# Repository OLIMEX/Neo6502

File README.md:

# Neo6502
Neo6502 Modern Retro Computer with W65C02S processor and RP2040 memory and peripherals emulator

Neo6502 is small board with dimensions 80x55mm.

it consist of real W65C02S processor and RP2040 which emulates RAM memory, video, keyboard, SPI, I2C, UART, GPIOs, Sound

## Intro

W65C02S lives in The Matrix and thinks there is real RAM and other interfaces around it, but the truth is that all this is emulation of the real life. The RP2040 emulates the RAM memory, video, IO and even clock the W65C02S by PWM.

## Features

Neo6502 has these features:

* W65C02S processor
* RP2040 SOC with 2MB Flash
* DVI video on HDMI connector
* USB host for keyboard
* Audio 3.5mm output
* Speaker with enable jumper
* USB-C for power supply
* UEXT connector with I2C, UART and SPI
* 40 pin 6502 bus connector with all W65C02 signals
* Dimensions 80x55mm
* 4 mount holes

## Licenses

* Hardware is released under CERN Open Hardware Licence Version 2 - Strongly Reciprocal, all silkscreen credits to Olimex should remain;
* Software is released under GPL3 Licensee
* Documentation is released under CC BY-SA 3.0

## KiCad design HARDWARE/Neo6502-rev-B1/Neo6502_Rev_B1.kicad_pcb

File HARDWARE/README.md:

Contains hardware design files for Olimex Neo6502

Board was designed with free Open Source CAD software - KiCAD, if you have trouble opening the design files use newest KiCAD version.

Folder "3D printed Case" contains STL files for multi material 3D printing of the encolosure.

STL files are designed with Fusion 360

Notable hardware revision changes:

revision B1
======
1. Added diode 1N5819/S4 on FUSE1 pads to enable 5V on HDMI (diode is used to prevent HDMI powering the board). You can try this adjustmest if you have older revision (with nothing placed over FUSE1) and problems with monitor, remember diode has direction and cathode has to be towards the HDMI connector.

revision B
======

1. Changed values P-B-V-40-LF and P-B-V-10-LF;
2. R7 set to 47R/R1206;
3. Added SWITCH1 for the speaker and signals go to the UEXT in case somebody needs them;
4. Added Neo6502 logo;
5. R1 changed NA to 10K;
6. Added attributions names and e-mail at the bottom;
7. C15 and C16 now 18pF;
8. A lot of small adjustmets to reduce soldering problems and yield.

revision A
======

Initial release.

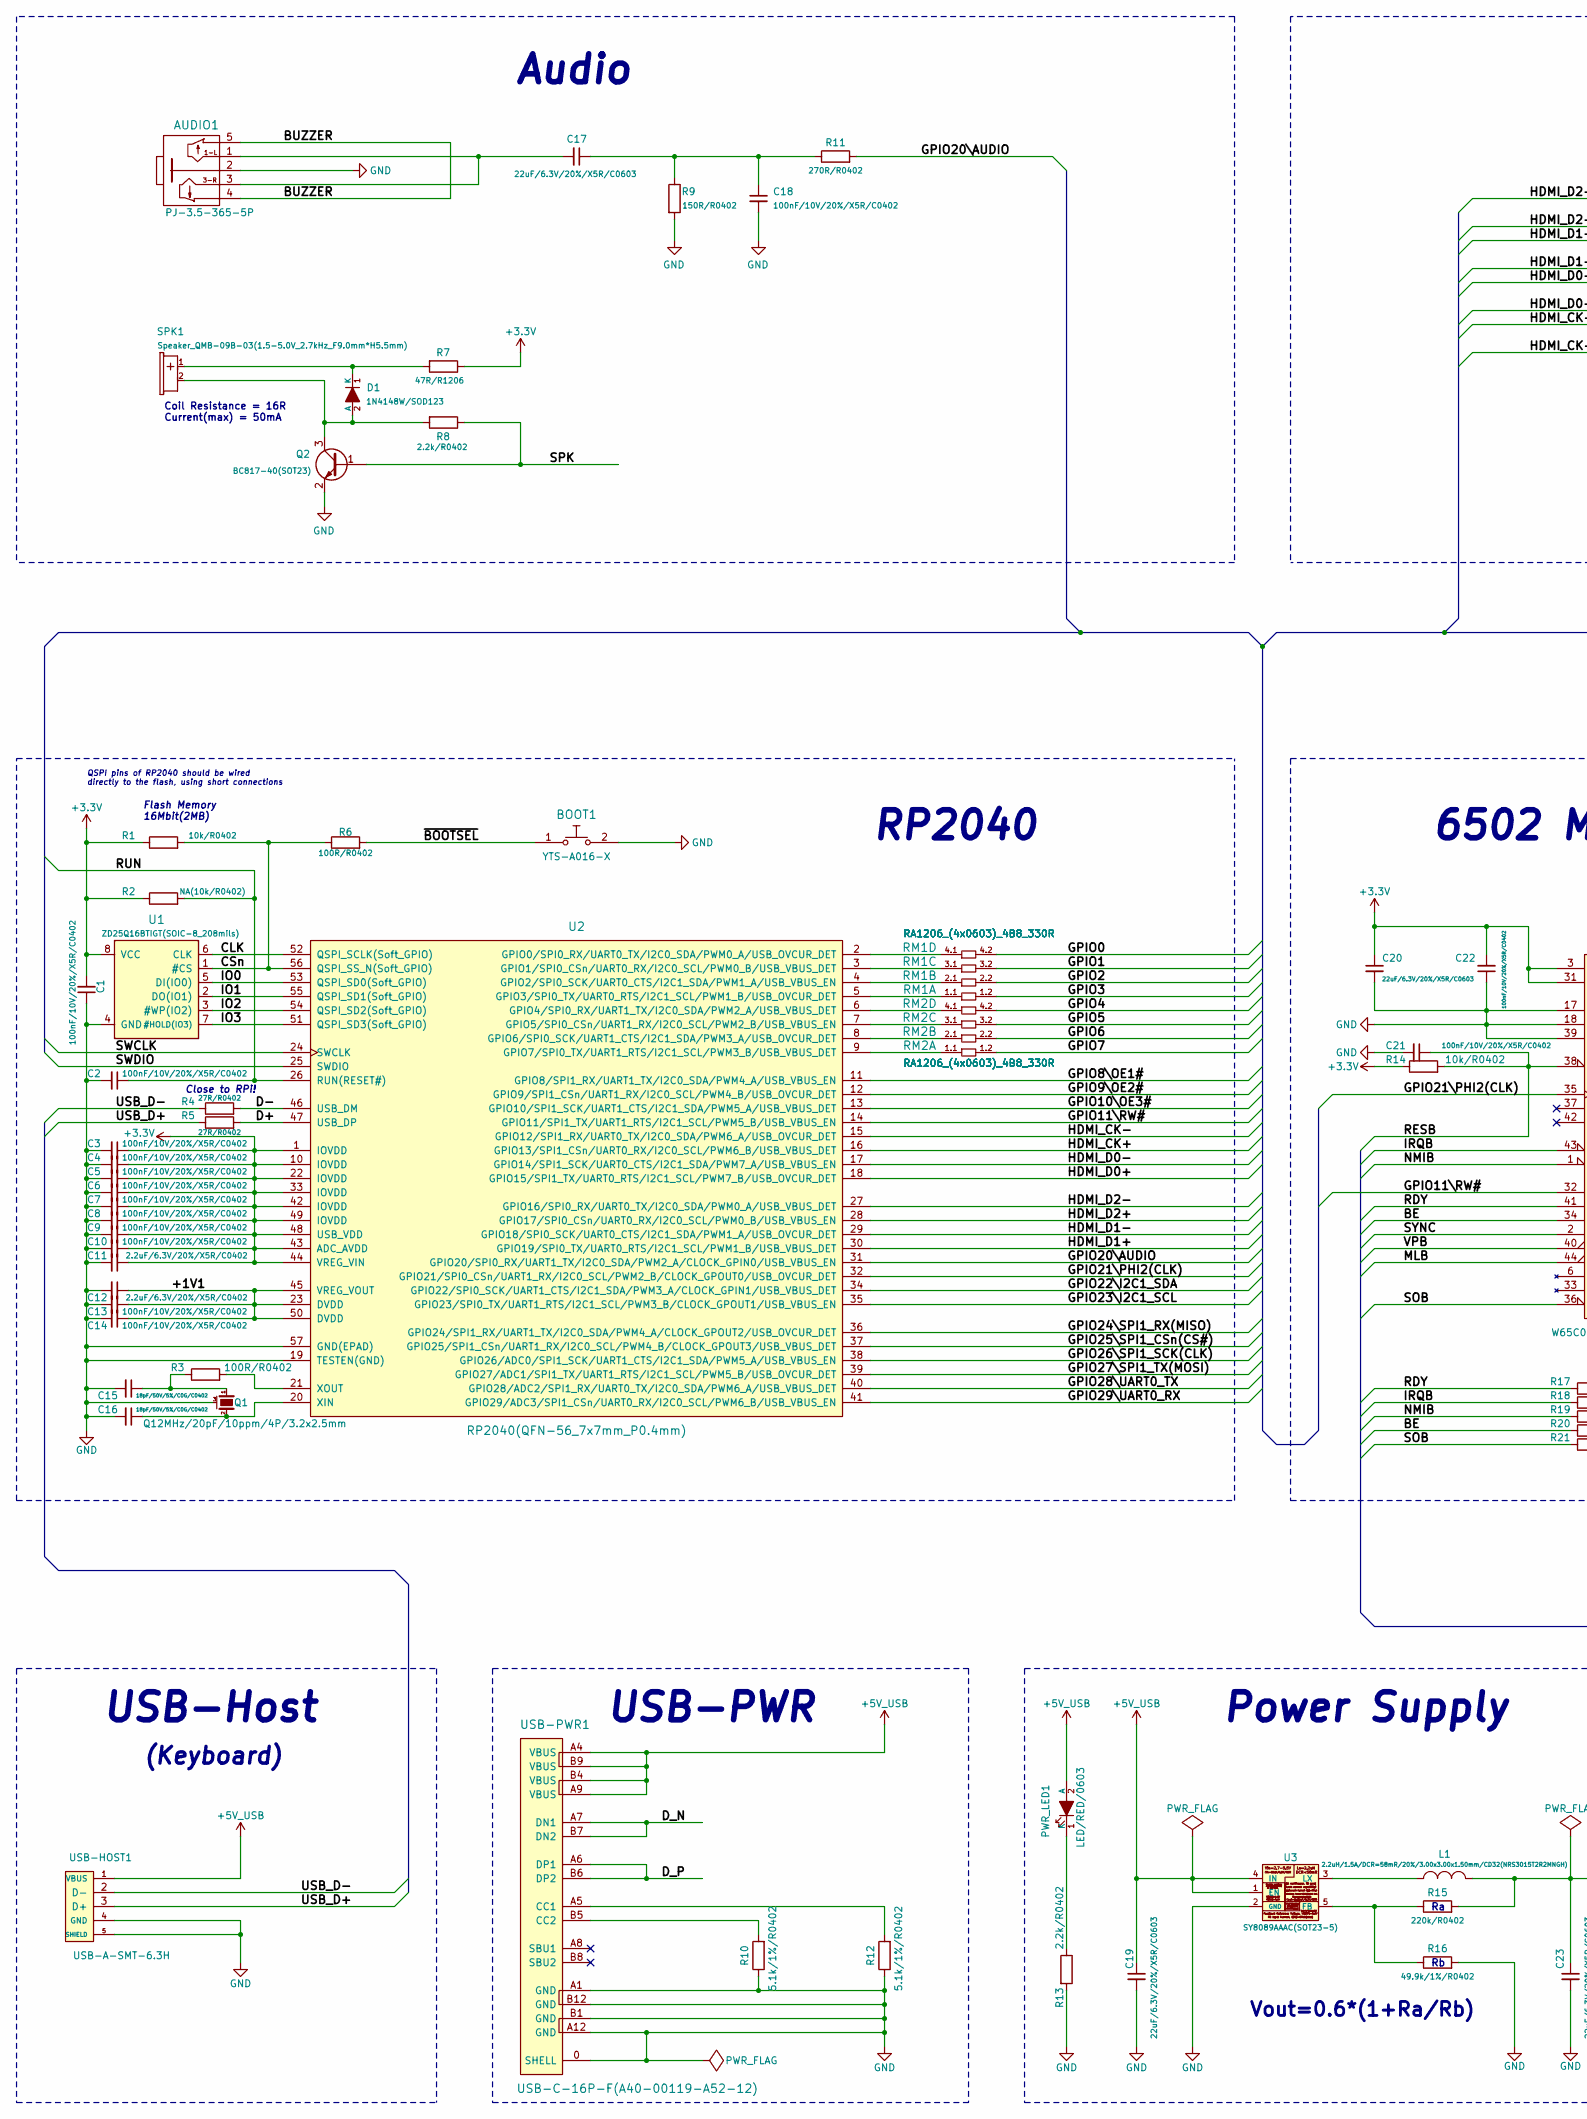
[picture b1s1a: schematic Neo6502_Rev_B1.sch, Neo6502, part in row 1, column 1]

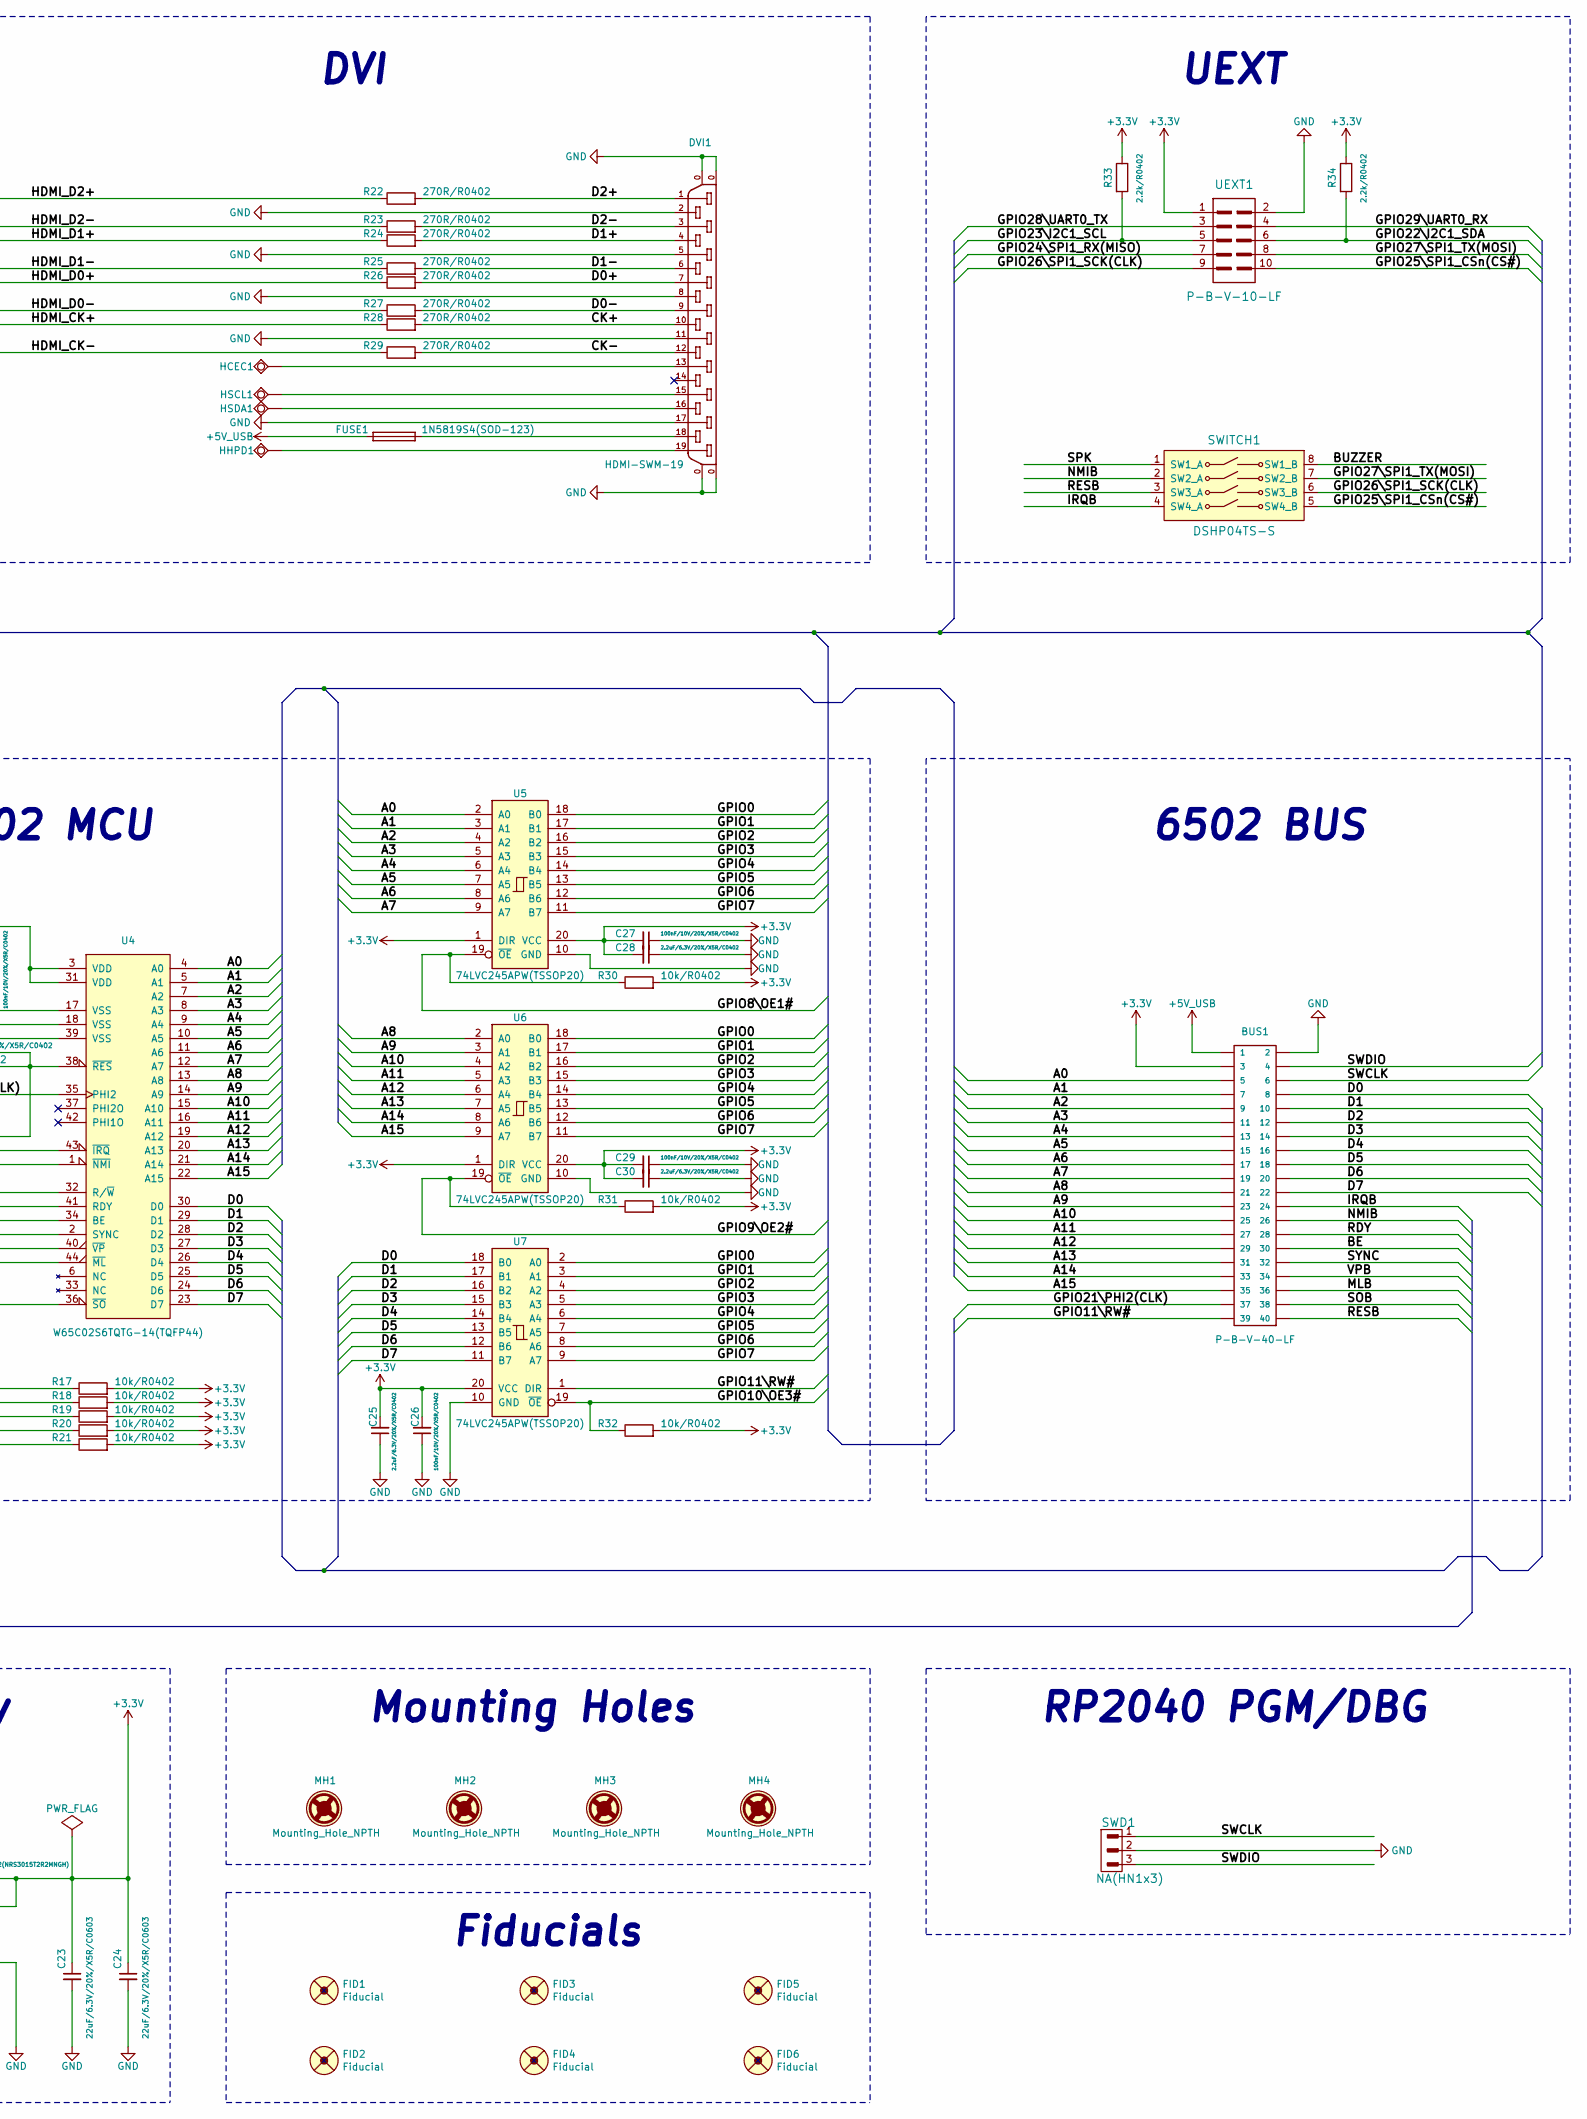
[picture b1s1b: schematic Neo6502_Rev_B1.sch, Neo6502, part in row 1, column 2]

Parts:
AUDIO1: PJ-3.5-365-5P; SCJ325P00XG0B02G
BOOT1: YTS-A016-X
BUS1: P-B-V-40-LF; GBH-254-SMT-40
C1, C2, C3, C4, C5, C6, C7, C8, C9, C10, C13, C14, C18, C21, C22, C26, C27, C29: 100nF/10V/20%/X5R/C0402; C_0402_5MIL_DWS
C11, C12, C25, C28, C30: 2.2uF/6.3V/20%/X5R/C0402; C_0402_5MIL_DWS
C15, C16: 18pF/50V/5%/C0G/C0402; C_0402_5MIL_DWS
C17, C19, C20, C23, C24: 22uF/6.3V/20%/X5R/C0603; C_0603_5MIL_DWS
D1: 1N4148W/SOD123; SOD-123_1C-2A_KA
DVI1: HDMI-SWM-19; HDMI-SWM-19_Paste
FID1: Fiducial; Fiducial1x3_Past
FID2, FID3, FID4, FID5, FID6: Fiducial; Fiducial1x3
FUSE1: 1N5819S4(SOD-123); FUSE-1206
HCEC1: TESTPAD; TESTPAD_40-ROUND
HHPD1: TESTPAD; TESTPAD_40-ROUND
HSCL1: TESTPAD; TESTPAD_40-ROUND
HSDA1: TESTPAD; TESTPAD_40-ROUND
L1: 2.2uH/1.5A/DCR=58mR/20%/3.00x3.00x1.50mm/CD32(NRS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; CD32
MH1, MH2, MH3, MH4: Mounting_Hole_NPTH; Mounting_Hole_Drill-3.3mm_Clerance-7mm
PWR_LED1: LED/RED/0603; LED_0603_KA
Q1: Q12MHz/20pF/10ppm/4P/3.2x2.5mm; TSX-3.2x2.5mm_GND(3)
Q2: BC817-40(SOT23); SOT23
R1, R14, R17, R18, R19, R20, R21, R30, R31, R32: 10k/R0402; R_0402_5MIL_DWS
R2: NA(10k/R0402); R_0402_5MIL_DWS
R3, R6: 100R/R0402; R_0402_5MIL_DWS
R4, R5: 27R/R0402; R_0402_5MIL_DWS
R7: 47R/R1206; R_1206_5MIL_DWS
R8, R13, R33, R34: 2.2k/R0402; R_0402_5MIL_DWS
R9: 150R/R0402; R_0402_5MIL_DWS
R10, R12: 5.1k/1%/R0402; R_0402_5MIL_DWS
R11, R22, R23, R24, R25, R26, R27, R28, R29: 270R/R0402; R_0402_5MIL_DWS
R15: 220k/R0402; R_0402_5MIL_DWS
R16: 49.9k/1%/R0402; R_0402_5MIL_DWS
RM1, RM2: RA1206_(4x0603)_4B8_330R; RA1206_(4X0603)_4B8_xx
SPK1: Speaker_QMB-09B-03(1.5-5.0V_2.7kHz_F9.0mm*H5.5mm); Speaker_QMB-09B-03_1-Plus_2-Minus
SWD1: NA(HN1x3); HN1x3
SWITCH1: DSHP04TS-S; DSHP04TS-S-1.27mm_Half_4_Slide
U1: ZD25Q16BTIGT(SOIC-8_208mils); SO-8_208mil
U2: RP2040(QFN-56_7x7mm_P0.4mm); QFN56_7x7_Pitch_0.4mm
U3: SY8089AAAC(SOT23-5); SOT-23-5
U4: W65C02S6TQTG-14(TQFP44); TQFP44_NEO6502
U5, U6, U7: 74LVC245APW(TSSOP20); TSSOP20_Pitch-0.65mm_6.6x4.5x1.2mm
UEXT1: P-B-V-10-LF; GBH-254-SMT-10
USB-HOST1: USB-A-SMT-6.3H; USB-A-SMT-6.3H_HOST_Female
USB-PWR1: USB-C-16P-F(A40-00119-A52-12); USB2.0_TYPE-C(A40-00119-A52-12)_Paste

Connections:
+3.3V: BUS1.3, C1.2, C3.1, C4.1, C5.1, C6.1, C7.1, C8.1, C9.1, C10.1, C11.1, C20.1, C22.2, C23.1, C24.1, C25.2, C26.2, C27.2, C28.2, C29.2, C30.2, L1.2, R1.1, R2.1, R7.1, R14.1, R15.2, R17.2, R18.2, R19.2, R20.2, R21.2, R30.2, R31.2, R32.2, R33.1, R34.1, U1.8 (VCC), U2.1 (IOVDD), U2.10 (IOVDD), U2.22 (IOVDD), U2.33 (IOVDD), U2.42 (IOVDD), U2.43 (ADC_AVDD), U2.44 (VREG_VIN), U2.48 (USB_VDD), U2.49 (IOVDD), U4.3 (VDD), U4.31 (VDD), U5.1 (DIR), U5.20 (VCC), U6.1 (DIR), U6.20 (VCC), U7.20 (VCC), UEXT1.1
+5V_USB: BUS1.1, C19.1, FUSE1.1, PWR_LED1.2 (A), U3.1 (EN), U3.4 (IN), USB-HOST1.1 (VBUS), USB-PWR1.A4 (VBUS), USB-PWR1.A9 (VBUS), USB-PWR1.B4 (VBUS), USB-PWR1.B9 (VBUS)
/+1V1: C12.1, C13.1, C14.1, U2.23 (DVDD), U2.45 (VREG_VOUT), U2.50 (DVDD)
/A0: BUS1.5, U4.4 (A0), U5.2 (A0)
/A1: BUS1.7, U4.5 (A1), U5.3 (A1)
/A2: BUS1.9, U4.7 (A2), U5.4 (A2)
/A3: BUS1.11, U4.8 (A3), U5.5 (A3)
/A4: BUS1.13, U4.9 (A4), U5.6 (A4)
/A5: BUS1.15, U4.10 (A5), U5.7 (A5)
/A6: BUS1.17, U4.11 (A6), U5.8 (A6)
/A7: BUS1.19, U4.12 (A7), U5.9 (A7)
/A8: BUS1.21, U4.13 (A8), U6.2 (A0)
/A9: BUS1.23, U4.14 (A9), U6.3 (A1)
/A10: BUS1.25, U4.15 (A10), U6.4 (A2)
/A11: BUS1.27, U4.16 (A11), U6.5 (A3)
/A12: BUS1.29, U4.19 (A12), U6.6 (A4)
/A13: BUS1.31, U4.20 (A13), U6.7 (A5)
/A14: BUS1.33, U4.21 (A14), U6.8 (A6)
/A15: BUS1.35, U4.22 (A15), U6.9 (A7)
/BE: BUS1.30, R20.1, U4.34 (BE)
/BUZZER: AUDIO1.4, AUDIO1.5, SWITCH1.8 (SW1_B)
/CK+: DVI1.10, R28.2
/CK-: DVI1.12, R29.2
/CLK: U1.6 (CLK), U2.52 (QSPI_SCLK(Soft_GPIO))
/CSn: R1.2, R6.1, U1.1 (#CS), U2.56 (QSPI_SS_N(Soft_GPIO))
/D0: BUS1.8, U4.30 (D0), U7.18 (B0)
/D0+: DVI1.7, R26.2
/D0-: DVI1.9, R27.2
/D1: BUS1.10, U4.29 (D1), U7.17 (B1)
/D1+: DVI1.4, R24.2
/D1-: DVI1.6, R25.2
/D2: BUS1.12, U4.28 (D2), U7.16 (B2)
/D2+: DVI1.1, R22.2
/D2-: DVI1.3, R23.2
/D3: BUS1.14, U4.27 (D3), U7.15 (B3)
/D4: BUS1.16, U4.26 (D4), U7.14 (B4)
/D5: BUS1.18, U4.25 (D5), U7.13 (B5)
/D6: BUS1.20, U4.24 (D6), U7.12 (B6)
/D7: BUS1.22, U4.23 (D7), U7.11 (B7)
/D+: R5.2, U2.47 (USB_DP)
/D-: R4.2, U2.46 (USB_DM)
/D_N: USB-PWR1.A7 (DN1), USB-PWR1.B7 (DN2)
/D_P: USB-PWR1.A6 (DP1), USB-PWR1.B6 (DP2)
/GPIO0: RM1.4.2, U5.18 (B0), U6.18 (B0), U7.2 (A0)
/GPIO1: RM1.3.2, U5.17 (B1), U6.17 (B1), U7.3 (A1)
/GPIO2: RM1.2.2, U5.16 (B2), U6.16 (B2), U7.4 (A2)
/GPIO3: RM1.1.2, U5.15 (B3), U6.15 (B3), U7.5 (A3)
/GPIO4: RM2.4.2, U5.14 (B4), U6.14 (B4), U7.6 (A4)
/GPIO5: RM2.3.2, U5.13 (B5), U6.13 (B5), U7.7 (A5)
/GPIO6: RM2.2.2, U5.12 (B6), U6.12 (B6), U7.8 (A6)
/GPIO7: RM2.1.2, U5.11 (B7), U6.11 (B7), U7.9 (A7)
/GPIO8\OE1#: R30.1, U2.11 (GPIO8/SPI1_RX/UART1_TX/I2C0_SDA/PWM4_A/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), U5.19 (~OE)
/GPIO9\OE2#: R31.1, U2.12 (GPIO9/SPI1_CSn/UART1_RX/I2C0_SCL/PWM4_B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), U6.19 (~OE)
/GPIO10\OE3#: R32.1, U2.13 (GPIO10/SPI1_SCK/UART1_CTS/I2C1_SDA/PWM5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), U7.19 (~OE)
/GPIO11\RW#: BUS1.39, U2.14 (GPIO11/SPI1_TX/UART1_RTS/I2C1_SCL/PWM5_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), U4.32 (R/~W), U7.1 (DIR)
/GPIO20\AUDIO: R11.2, U2.31 (GPIO20/SPI0_RX/UART1_TX/I2C0_SDA/PWM2_A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)
/GPIO21\PHI2(CLK): BUS1.37, U2.32 (GPIO21/SPI0_CSn/UART1_RX/I2C0_SCL/PWM2_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), U4.35 (PHI2)
/GPIO22\I2C1_SDA: R34.2, U2.34 (GPIO22/SPI0_SCK/UART1_CTS/I2C1_SDA/PWM3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), UEXT1.6
/GPIO23\I2C1_SCL: R33.2, U2.35 (GPIO23/SPI0_TX/UART1_RTS/I2C1_SCL/PWM3_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), UEXT1.5
/GPIO24\SPI1_RX(MISO): U2.36 (GPIO24/SPI1_RX/UART1_TX/I2C0_SDA/PWM4_A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), UEXT1.7
/GPIO25\SPI1_CSn(CS#): SWITCH1.5 (SW4_B), U2.37 (GPIO25/SPI1_CSn/UART1_RX/I2C0_SCL/PWM4_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), UEXT1.10
/GPIO26\SPI1_SCK(CLK): SWITCH1.6 (SW3_B), U2.38 (GPIO26/ADC0/SPI1_SCK/UART1_CTS/I2C1_SDA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), UEXT1.9
/GPIO27\SPI1_TX(MOSI): SWITCH1.7 (SW2_B), U2.39 (GPIO27/ADC1/SPI1_TX/UART1_RTS/I2C1_SCL/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), UEXT1.8
/GPIO28\UART0_TX: U2.40 (GPIO28/ADC2/SPI1_RX/UART0_TX/I2C0_SDA/P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), UEXT1.3
/GPIO29\UART0_RX: U2.41 (GPIO29/ADC3/SPI1_CSn/UART0_RX/I2C0_SCL/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), UEXT1.4
/HDMI_CK+: R28.1, U2.16 (GPIO13/SPI1_CSn/UART0_RX/I2C0_SCL/PWM6_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)
/HDMI_CK-: R29.1, U2.15 (GPIO12/SPI1_RX/UART0_TX/I2C0_SDA/PWM6_A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)
/HDMI_D0+: R26.1, U2.18 (GPIO15/SPI1_TX/UART0_RTS/I2C1_SCL/PWM7_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)
/HDMI_D0-: R27.1, U2.17 (GPIO14/SPI1_SCK/UART0_CTS/I2C1_SDA/PWM7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)
/HDMI_D1+: R24.1, U2.30 (GPIO19/SPI0_TX/UART0_RTS/I2C1_SCL/PWM1_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)
/HDMI_D1-: R25.1, U2.29 (GPIO18/SPI0_SCK/UART0_CTS/I2C1_SDA/PWM1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)
/HDMI_D2+: R22.1, U2.28 (GPIO17/SPI0_CSn/UART0_RX/I2C0_SCL/PWM0_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)
/HDMI_D2-: R23.1, U2.27 (GPIO16/SPI0_RX/UART0_TX/I2C0_SDA/PWM0_A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)
/IO0: U1.5 (DI(IO0)), U2.53 (QSPI_SD0(Soft_GPIO))
/IO1: U1.2 (DO(IO1)), U2.55 (QSPI_SD1(Soft_GPIO))
/IO2: U1.3 (#WP(IO2)), U2.54 (QSPI_SD2(Soft_GPIO))
/IO3: U1.7 (#HOLD(IO3)), U2.51 (QSPI_SD3(Soft_GPIO))
/IRQB: BUS1.24, R18.1, SWITCH1.4 (SW4_A), U4.43 (~IRQ)
/MLB: BUS1.36, U4.44 (~ML)
/NMIB: BUS1.26, R19.1, SWITCH1.2 (SW2_A), U4.1 (~NMI)
/RDY: BUS1.28, R17.1, U4.41 (RDY)
/RESB: BUS1.40, C21.1, R14.2, SWITCH1.3 (SW3_A), U4.38 (~RES)
/RUN: C2.1, R2.2, U2.26 (RUN(RESET#))
/SOB: BUS1.38, R21.1, U4.36 (~SO)
/SPK: Q2.1 (B), R8.1, SWITCH1.1 (SW1_A)
/SWCLK: BUS1.6, SWD1.1, U2.24 (SWCLK)
/SWDIO: BUS1.4, SWD1.3, U2.25 (SWDIO)
/SYNC: BUS1.32, U4.2 (SYNC)
/USB_D+: R5.1, USB-HOST1.3 (D+)
/USB_D-: R4.1, USB-HOST1.2 (D-)
/VPB: BUS1.34, U4.40 (~VP)
/~BOOTSEL: BOOT1.1, R6.2
GND: AUDIO1.2, BOOT1.2, BUS1.2, C1.1, C2.2, C3.2, C4.2, C5.2, C6.2, C7.2, C8.2, C9.2, C10.2, C11.2, C12.2, C13.2, C14.2, C15.2, C16.2, C18.2, C19.2, C20.2, C21.2, C22.1, C23.2, C24.2, C25.1, C26.1, C27.1, C28.1, C29.1, C30.1, DVI1.0 (20), DVI1.2, DVI1.5, DVI1.8, DVI1.11, DVI1.17, Q1.3 (case), Q2.2 (E), R9.2, R10.1, R12.1, R13.2, R16.2, SWD1.2, U1.4 (GND), U2.19 (TESTEN(GND)), U2.57 (GND(EPAD)), U3.2 (GND), U4.17 (VSS), U4.18 (VSS), U4.39 (VSS), U5.10 (GND), U6.10 (GND), U7.10 (GND), UEXT1.2, USB-HOST1.4 (GND), USB-HOST1.5 (SHIELD), USB-PWR1.0 (SHELL), USB-PWR1.A1 (GND), USB-PWR1.A12 (GND), USB-PWR1.B1 (GND), USB-PWR1.B12 (GND)
unnamed: AUDIO1.1, AUDIO1.3, C17.2
unnamed: C15.1, Q1.1, R3.1
unnamed: C16.1, Q1.2, U2.20 (XIN)
unnamed: C17.1, C18.1, R9.1, R11.1
unnamed: D1.1 (K), R7.2, SPK1.1 (PLUS)
unnamed: D1.2 (A), Q2.3 (C), R8.2, SPK1.2 (MINUS)
unnamed: DVI1.13, HCEC1.1
unnamed: DVI1.15, HSCL1.1
unnamed: DVI1.16, HSDA1.1
unnamed: DVI1.18, FUSE1.2
unnamed: DVI1.19, HHPD1.1
unnamed: L1.1, U3.3 (LX)
unnamed: PWR_LED1.1 (K), R13.1
unnamed: R3.2, U2.21 (XOUT)
unnamed: R10.2, USB-PWR1.B5 (CC2)
unnamed: R12.2, USB-PWR1.A5 (CC1)
unnamed: R15.1, R16.1, U3.5 (FB)
unnamed: RM1.1.1, U2.5 (GPIO3/SPI0_TX/UART0_RTS/I2C1_SCL/PWM1_B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)
unnamed: RM1.2.1, U2.4 (GPIO2/SPI0_SCK/UART0_CTS/I2C1_SDA/PWM1_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)
unnamed: RM1.3.1, U2.3 (GPIO1/SPI0_CSn/UART0_RX/I2C0_SCL/PWM0_B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)
unnamed: RM1.4.1, U2.2 (GPIO0/SPI0_RX/UART0_TX/I2C0_SDA/PWM0_A/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)
unnamed: RM2.1.1, U2.9 (GPIO7/SPI0_TX/UART1_RTS/I2C1_SCL/PWM3_B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)
unnamed: RM2.2.1, U2.8 (GPIO6/SPI0_SCK/UART1_CTS/I2C1_SDA/PWM3_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)
unnamed: RM2.3.1, U2.7 (GPIO5/SPI0_CSn/UART1_RX/I2C0_SCL/PWM2_B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)
unnamed: RM2.4.1, U2.6 (GPIO4/SPI0_RX/UART1_TX/I2C0_SDA/PWM2_A/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)

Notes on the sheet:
Fiducials
Mounting Holes
Audio
UEXT
6502 BUS
Power Supply
Vout=0.6*(1+Ra/Rb)
Flash Memory 16Mbit(2MB)
Close to RPi!
QSPI pins of RP2040 should be wired directly to the flash, using short connections
USB-PWR
RP2040
6502 MCU
USB-Host
(Keyboard)
DVI
RP2040 PGM/DBG
Coil Resistance = 16R Current(max) = 50mA

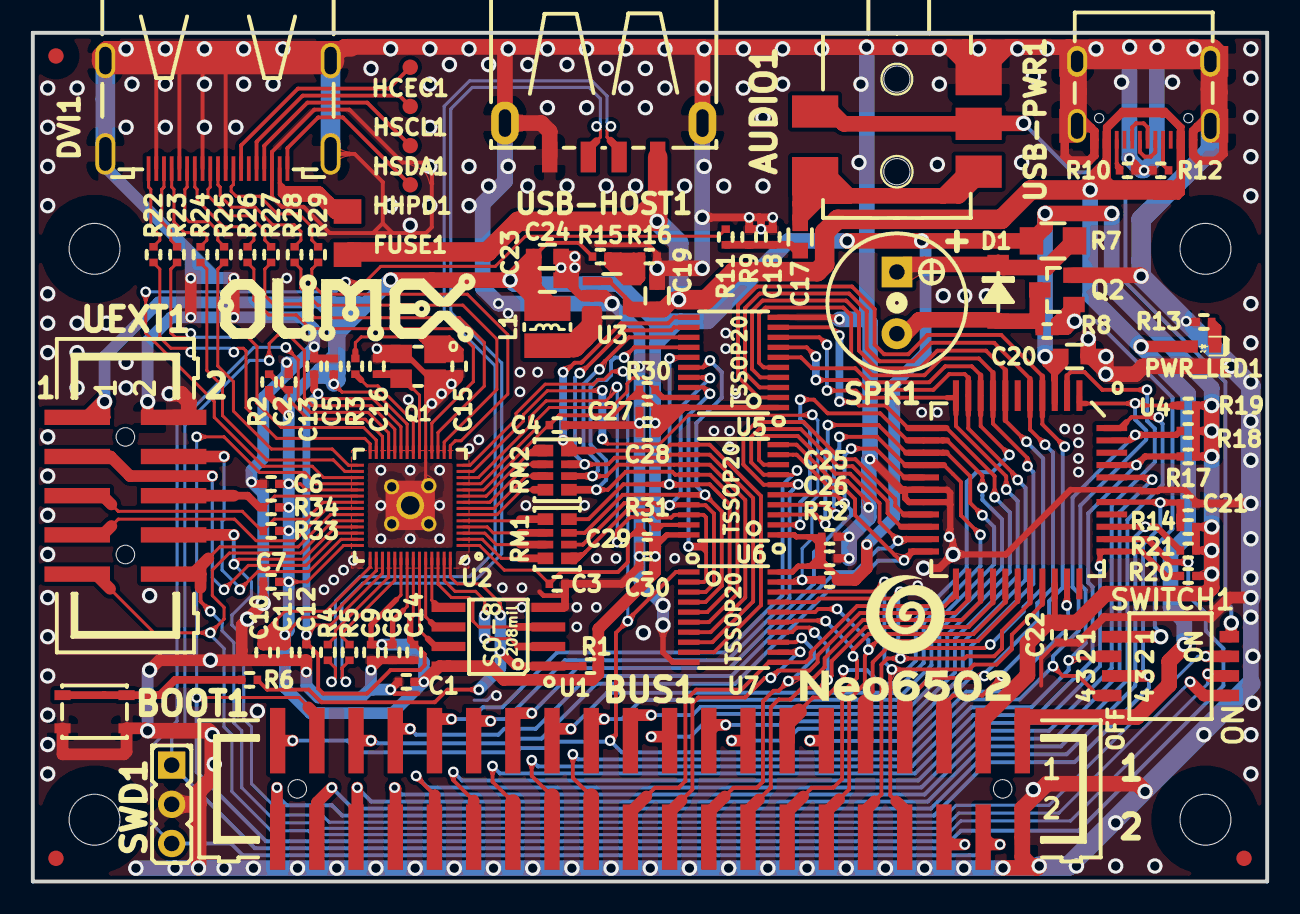
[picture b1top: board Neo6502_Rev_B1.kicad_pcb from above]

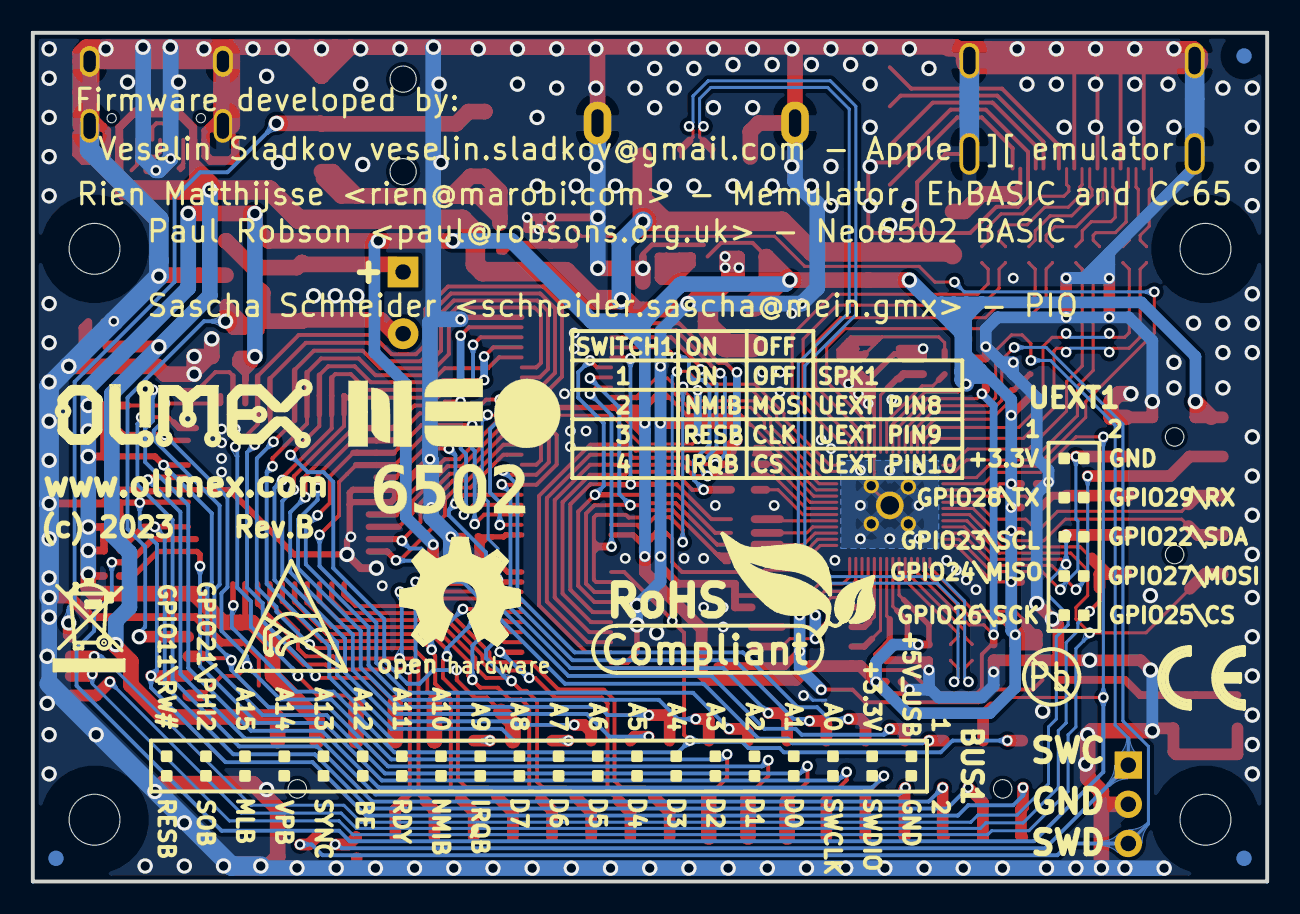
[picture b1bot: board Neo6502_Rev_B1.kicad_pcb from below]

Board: 2 copper layers, 80.0 x 55.0 mm, 113 parts (11 on the bottom side), 118 nets.

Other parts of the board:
Logo_OLIMEX_TB-Bottom: Logo_OLIMEX_TB
Logo_OLIMEX_TB-Top: Logo_OLIMEX_TB
NEO6502_NEW: LOGO; Neo6502_Sign_Small_NEW2
NEO_LOGO_SMALL*: LOGO; Neo6502_Sign_Small
Sign_Antistatic: Sign_Antistatic
Sign_CE: CE_Sign
Sign_OSHW_8x8: Sign_OSHW_8x8
Sign_PB-Free: Sign_PB-Free
Sign_RecycleBin: Sign_RecycleBin; Sign_RecycleBin_1
Sign_RoHS: Sign_RoHS; Sign_RoHS_1

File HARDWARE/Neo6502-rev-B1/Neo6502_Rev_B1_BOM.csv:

"Id";"Designator";"Package";"Quantity";"Designation";"Supplier and ref";
1;"USB-PWR1";"USB2.0_TYPE-C(A40-00119-A52-12)_Paste";1;"USB-C-16P-F(A40-00119-A52-12)";;;
2;"NEO6502_NEW";"Neo6502_Sign_Small_NEW2";1;"LOGO";;;
3;"NEO_LOGO_SMALL*";"Neo6502_Sign_Small";1;"LOGO";;;
4;"USB-HOST1";"USB-A-SMT-6.3H_HOST_Female";1;"USB-A-SMT-6.3H";;;
5;"DVI1";"HDMI-SWM-19_Paste";1;"HDMI-SWM-19";;;
6;"BUS1";"GBH-254-SMT-40";1;"P-B-V-40-LF";;;
7;"UEXT1";"GBH-254-SMT-10";1;"P-B-V-10-LF";;;
8;"Sign_RoHS";"Sign_RoHS_1";1;"Sign_RoHS";;;
9;"Sign_RecycleBin";"Sign_RecycleBin_1";1;"Sign_RecycleBin";;;
10;"Sign_PB-Free";"Sign_PB-Free";1;"Sign_PB-Free";;;
11;"Sign_OSHW_8x8";"Sign_OSHW_8x8";1;"Sign_OSHW_8x8";;;
12;"Sign_Antistatic";"Sign_Antistatic";1;"Sign_Antistatic";;;
13;"Logo_OLIMEX_TB-Bottom,Logo_OLIMEX_TB-Top";"Logo_OLIMEX_TB";2;"Logo_OLIMEX_TB";;;
14;"Sign_CE";"CE_Sign";1;"CE_Sign";;;
15;"AUDIO1";"SCJ325P00XG0B02G";1;"PJ-3.5-365-5P";;;
16;"C22,C18,C1,C2,C3,C4,C5,C6,C7,C8,C9,C10,C13,C14,C21,C26,C27,C29";"C_0402_5MIL_DWS";18;"100nF/10V/20%/X5R/C0402";;;
17;"FID2,FID3,FID5,FID6,FID4";"Fiducial1x3";5;"Fiducial";;;
18;"MH1,MH2,MH3,MH4";"Mounting_Hole_Drill-3.3mm_Clerance-7mm";4;"Mounting_Hole_NPTH";;;
19;"PWR_LED1";"LED_0603_KA";1;"LED/RED/0603";;;
20;"R13,R33,R34,R8";"R_0402_5MIL_DWS";4;"2.2k/R0402";;;
21;"R30,R1,R14,R17,R18,R19,R20,R21,R31,R32";"R_0402_5MIL_DWS";10;"10k/R0402";;;
22;"R9";"R_0402_5MIL_DWS";1;"150R/R0402";;;
23;"R11,R22,R23,R24,R25,R26,R27,R28,R29";"R_0402_5MIL_DWS";9;"270R/R0402";;;
24;"C20,C17,C19,C23,C24";"C_0603_5MIL_DWS";5;"22uF/6.3V/20%/X5R/C0603";;;
25;"D1";"SOD-123_1C-2A_KA";1;"1N4148W/SOD123";;;
26;"Q2";"SOT23";1;"BC817-40(SOT23)";;;
27;"BOOT1";"YTS-A016-X";1;"YTS-A016-X";;;
28;"C11,C12,C25,C28,C30";"C_0402_5MIL_DWS";5;"2.2uF/6.3V/20%/X5R/C0402";;;
29;"C15,C16";"C_0402_5MIL_DWS";2;"18pF/50V/5%/C0G/C0402";;;
30;"HCEC1,HHPD1,HSCL1,HSDA1";"TESTPAD_40-ROUND";4;"TESTPAD";;;
31;"FUSE1";"FUSE-1206";1;"1N5819S4(SOD-123)";;;
32;"L1";"CD32";1;"2.2uH/1.5A/DCR=58mR/20%/3.00x3.00x1.50mm/CD32(NRS3015T2R2MNGH)";;;
33;"Q1";"TSX-3.2x2.5mm_GND(3)";1;"Q12MHz/20pF/10ppm/4P/3.2x2.5mm";;;
34;"R2";"R_0402_5MIL_DWS";1;"NA(10k/R0402)";;;
35;"R3,R6";"R_0402_5MIL_DWS";2;"100R/R0402";;;
36;"R4,R5";"R_0402_5MIL_DWS";2;"27R/R0402";;;
37;"R10,R12";"R_0402_5MIL_DWS";2;"5.1k/1%/R0402";;;
38;"R15";"R_0402_5MIL_DWS";1;"220k/R0402";;;
39;"R16";"R_0402_5MIL_DWS";1;"49.9k/1%/R0402";;;
40;"RM1,RM2";"RA1206_(4X0603)_4B8_xx";2;"RA1206_(4x0603)_4B8_330R";;;
41;"SWD1";"HN1x3";1;"NA(HN1x3)";;;
42;"U1";"SO-8_208mil";1;"ZD25Q16BTIGT(SOIC-8_208mils)";;;
43;"U2";"QFN56_7x7_Pitch_0.4mm";1;"RP2040(QFN-56_7x7mm_P0.4mm)";;;
44;"U3";"SOT-23-5";1;"SY8089AAAC(SOT23-5)";;;
45;"U5,U6,U7";"TSSOP20_Pitch-0.65mm_6.6x4.5x1.2mm";3;"74LVC245APW(TSSOP20)";;;
46;"SPK1";"Speaker_QMB-09B-03_1-Plus_2-Minus";1;"Speaker_QMB-09B-03(1.5-5.0V_2.7kHz_F9.0mm*H5.5mm)";;;
47;"R7";"R_1206_5MIL_DWS";1;"47R/R1206";;;
48;"FID1";"Fiducial1x3_Past";1;"Fiducial";;;
49;"U4";"TQFP44_NEO6502";1;"W65C02S6TQTG-14(TQFP44)";;;
50;"SWITCH1";"DSHP04TS-S-1.27mm_Half_4_Slide";1;"DSHP04TS-S";;;

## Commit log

2023-06-26 initial upload
2023-07-04 add test software
2023-07-06 add memory emulator and Wozmon and MSBASIC
2023-07-06 memory emulator 1.0
2023-07-21 Update
    Revision A release files uploaded
2023-08-04 add usb2serial
2023-08-25 add Apple 2 emulator images
2023-08-25 colors fixed
2023-09-14 add loderunner
2023-10-03 rev.B
2023-10-11 adding 3d printed case with MMU option
2023-10-16 add user manual
2023-10-16 update user manual
2023-10-23 uploaded latest model files
2023-10-23 renamed bottom part
2024-06-11 Update
    Added revision B1 and added revision changes notes
2024-06-11 Update
    Updated manual, added FAQ
2024-07-10 reversal
2024-12-13 Update
    Update user manual
2025-07-22 Neo6502 user handbook
